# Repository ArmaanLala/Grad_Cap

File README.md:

# Graduation Cap
A PCB Design to wear on my Grad Cap for Spring 2023 commencement.

#### Important links

MicroController
https://www.adafruit.com/product/4481

## Schematic and Board layout

- Add images later

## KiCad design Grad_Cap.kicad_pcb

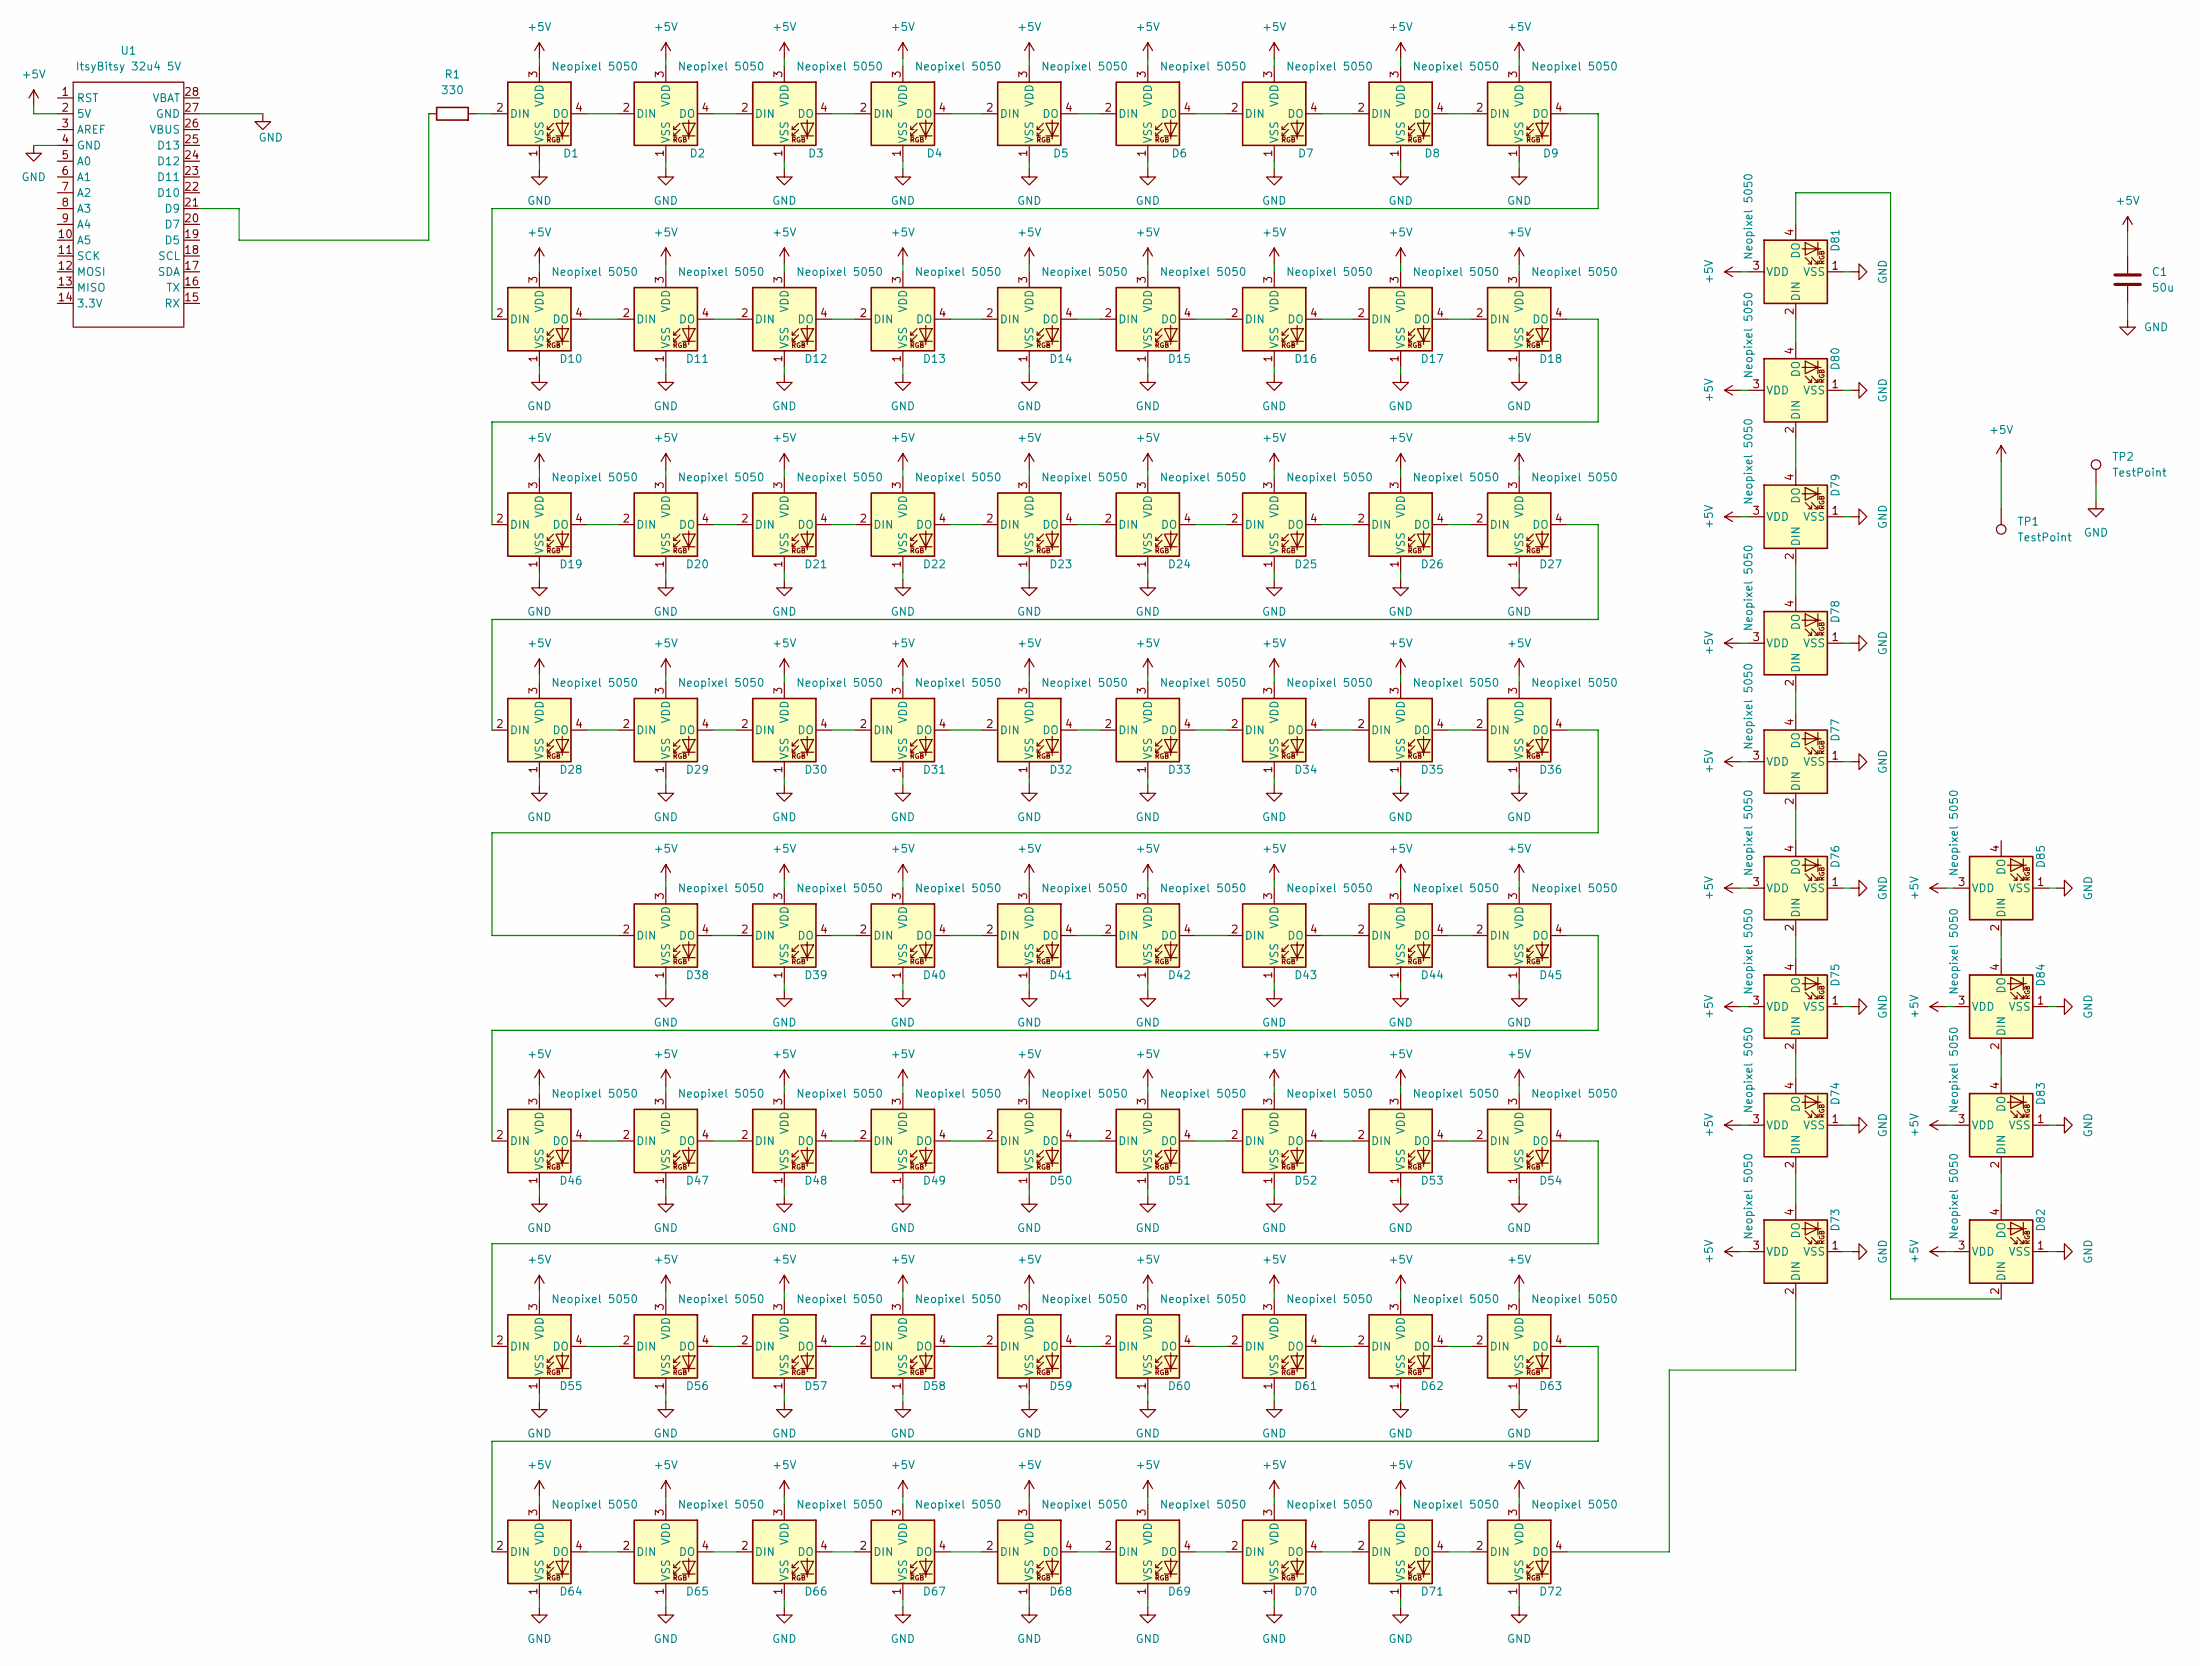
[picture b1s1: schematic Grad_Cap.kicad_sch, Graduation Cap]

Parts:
C1: 50u; C_1206_3216Metric_Pad1.33x1.80mm_HandSolder
D1, D2, D3, D4, D5, D6, D7, D8, D9, D10, D11, D12, D13, D14, D15, D16, D17, D18, D19, D20, D21, D22, D23, D24, D25, D26, D27, D28, D29, D30, D31, D32, D33, D34, D35, D36, D38, D39, D40, D41, D42, D43, D44, D45, D46, D47, D48, D49, D50, D51, D52, D53, D54, D55, D56, D57, D58, D59, D60, D61, D62, D63, D64, D65, D66, D67, D68, D69, D70, D71, D72, D73, D74, D75, D76, D77, D78, D79, D80, D81, D82, D83, D84, D85: Neopixel 5050; LED_Inolux_IN-PI554FCH_PLCC4_5.0x5.0mm_P3.2mm
R1: 330; R_1206_3216Metric_Pad1.30x1.75mm_HandSolder
TP1, TP2: TestPoint; TestPoint_Pad_4.0x4.0mm
U1: ItsyBitsy 32u4 5V; DIP-28_W15.24mm_LongPads

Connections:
+5V: C1.1, D1.3 (VDD), D2.3 (VDD), D3.3 (VDD), D4.3 (VDD), D5.3 (VDD), D6.3 (VDD), D7.3 (VDD), D8.3 (VDD), D9.3 (VDD), D10.3 (VDD), D11.3 (VDD), D12.3 (VDD), D13.3 (VDD), D14.3 (VDD), D15.3 (VDD), D16.3 (VDD), D17.3 (VDD), D18.3 (VDD), D19.3 (VDD), D20.3 (VDD), D21.3 (VDD), D22.3 (VDD), D23.3 (VDD), D24.3 (VDD), D25.3 (VDD), D26.3 (VDD), D27.3 (VDD), D28.3 (VDD), D29.3 (VDD), D30.3 (VDD), D31.3 (VDD), D32.3 (VDD), D33.3 (VDD), D34.3 (VDD), D35.3 (VDD), D36.3 (VDD), D38.3 (VDD), D39.3 (VDD), D40.3 (VDD), D41.3 (VDD), D42.3 (VDD), D43.3 (VDD), D44.3 (VDD), D45.3 (VDD), D46.3 (VDD), D47.3 (VDD), D48.3 (VDD), D49.3 (VDD), D50.3 (VDD), D51.3 (VDD), D52.3 (VDD), D53.3 (VDD), D54.3 (VDD), D55.3 (VDD), D56.3 (VDD), D57.3 (VDD), D58.3 (VDD), D59.3 (VDD), D60.3 (VDD), D61.3 (VDD), D62.3 (VDD), D63.3 (VDD), D64.3 (VDD), D65.3 (VDD), D66.3 (VDD), D67.3 (VDD), D68.3 (VDD), D69.3 (VDD), D70.3 (VDD), D71.3 (VDD), D72.3 (VDD), D73.3 (VDD), D74.3 (VDD), D75.3 (VDD), D76.3 (VDD), D77.3 (VDD), D78.3 (VDD), D79.3 (VDD), D80.3 (VDD), D81.3 (VDD), D82.3 (VDD), D83.3 (VDD), D84.3 (VDD), D85.3 (VDD), TP1.1, U1.2 (5V)
GND: C1.2, D1.1 (VSS), D2.1 (VSS), D3.1 (VSS), D4.1 (VSS), D5.1 (VSS), D6.1 (VSS), D7.1 (VSS), D8.1 (VSS), D9.1 (VSS), D10.1 (VSS), D11.1 (VSS), D12.1 (VSS), D13.1 (VSS), D14.1 (VSS), D15.1 (VSS), D16.1 (VSS), D17.1 (VSS), D18.1 (VSS), D19.1 (VSS), D20.1 (VSS), D21.1 (VSS), D22.1 (VSS), D23.1 (VSS), D24.1 (VSS), D25.1 (VSS), D26.1 (VSS), D27.1 (VSS), D28.1 (VSS), D29.1 (VSS), D30.1 (VSS), D31.1 (VSS), D32.1 (VSS), D33.1 (VSS), D34.1 (VSS), D35.1 (VSS), D36.1 (VSS), D38.1 (VSS), D39.1 (VSS), D40.1 (VSS), D41.1 (VSS), D42.1 (VSS), D43.1 (VSS), D44.1 (VSS), D45.1 (VSS), D46.1 (VSS), D47.1 (VSS), D48.1 (VSS), D49.1 (VSS), D50.1 (VSS), D51.1 (VSS), D52.1 (VSS), D53.1 (VSS), D54.1 (VSS), D55.1 (VSS), D56.1 (VSS), D57.1 (VSS), D58.1 (VSS), D59.1 (VSS), D60.1 (VSS), D61.1 (VSS), D62.1 (VSS), D63.1 (VSS), D64.1 (VSS), D65.1 (VSS), D66.1 (VSS), D67.1 (VSS), D68.1 (VSS), D69.1 (VSS), D70.1 (VSS), D71.1 (VSS), D72.1 (VSS), D73.1 (VSS), D74.1 (VSS), D75.1 (VSS), D76.1 (VSS), D77.1 (VSS), D78.1 (VSS), D79.1 (VSS), D80.1 (VSS), D81.1 (VSS), D82.1 (VSS), D83.1 (VSS), D84.1 (VSS), D85.1 (VSS), TP2.1, U1.4 (GND), U1.27 (GND)
unnamed: D1.2 (DIN), R1.2
unnamed: D1.4 (DO), D2.2 (DIN)
unnamed: D2.4 (DO), D3.2 (DIN)
unnamed: D3.4 (DO), D4.2 (DIN)
unnamed: D4.4 (DO), D5.2 (DIN)
unnamed: D5.4 (DO), D6.2 (DIN)
unnamed: D6.4 (DO), D7.2 (DIN)
unnamed: D7.4 (DO), D8.2 (DIN)
unnamed: D8.4 (DO), D9.2 (DIN)
unnamed: D9.4 (DO), D10.2 (DIN)
unnamed: D10.4 (DO), D11.2 (DIN)
unnamed: D11.4 (DO), D12.2 (DIN)
unnamed: D12.4 (DO), D13.2 (DIN)
unnamed: D13.4 (DO), D14.2 (DIN)
unnamed: D14.4 (DO), D15.2 (DIN)
unnamed: D15.4 (DO), D16.2 (DIN)
unnamed: D16.4 (DO), D17.2 (DIN)
unnamed: D17.4 (DO), D18.2 (DIN)
unnamed: D18.4 (DO), D19.2 (DIN)
unnamed: D19.4 (DO), D20.2 (DIN)
unnamed: D20.4 (DO), D21.2 (DIN)
unnamed: D21.4 (DO), D22.2 (DIN)
unnamed: D22.4 (DO), D23.2 (DIN)
unnamed: D23.4 (DO), D24.2 (DIN)
unnamed: D24.4 (DO), D25.2 (DIN)
unnamed: D25.4 (DO), D26.2 (DIN)
unnamed: D26.4 (DO), D27.2 (DIN)
unnamed: D27.4 (DO), D28.2 (DIN)
unnamed: D28.4 (DO), D29.2 (DIN)
unnamed: D29.4 (DO), D30.2 (DIN)
unnamed: D30.4 (DO), D31.2 (DIN)
unnamed: D31.4 (DO), D32.2 (DIN)
unnamed: D32.4 (DO), D33.2 (DIN)
unnamed: D33.4 (DO), D34.2 (DIN)
unnamed: D34.4 (DO), D35.2 (DIN)
unnamed: D35.4 (DO), D36.2 (DIN)
unnamed: D36.4 (DO), D38.2 (DIN)
unnamed: D38.4 (DO), D39.2 (DIN)
unnamed: D39.4 (DO), D40.2 (DIN)
unnamed: D40.4 (DO), D41.2 (DIN)
unnamed: D41.4 (DO), D42.2 (DIN)
unnamed: D42.4 (DO), D43.2 (DIN)
unnamed: D43.4 (DO), D44.2 (DIN)
unnamed: D44.4 (DO), D45.2 (DIN)
unnamed: D45.4 (DO), D46.2 (DIN)
unnamed: D46.4 (DO), D47.2 (DIN)
unnamed: D47.4 (DO), D48.2 (DIN)
unnamed: D48.4 (DO), D49.2 (DIN)
unnamed: D49.4 (DO), D50.2 (DIN)
unnamed: D50.4 (DO), D51.2 (DIN)
unnamed: D51.4 (DO), D52.2 (DIN)
unnamed: D52.4 (DO), D53.2 (DIN)
unnamed: D53.4 (DO), D54.2 (DIN)
unnamed: D54.4 (DO), D55.2 (DIN)
unnamed: D55.4 (DO), D56.2 (DIN)
unnamed: D56.4 (DO), D57.2 (DIN)
unnamed: D57.4 (DO), D58.2 (DIN)
unnamed: D58.4 (DO), D59.2 (DIN)
unnamed: D59.4 (DO), D60.2 (DIN)
unnamed: D60.4 (DO), D61.2 (DIN)
unnamed: D61.4 (DO), D62.2 (DIN)
unnamed: D62.4 (DO), D63.2 (DIN)
unnamed: D63.4 (DO), D64.2 (DIN)
unnamed: D64.4 (DO), D65.2 (DIN)
unnamed: D65.4 (DO), D66.2 (DIN)
unnamed: D66.4 (DO), D67.2 (DIN)
unnamed: D67.4 (DO), D68.2 (DIN)
unnamed: D68.4 (DO), D69.2 (DIN)
unnamed: D69.4 (DO), D70.2 (DIN)
unnamed: D70.4 (DO), D71.2 (DIN)
unnamed: D71.4 (DO), D72.2 (DIN)
unnamed: D72.4 (DO), D73.2 (DIN)
unnamed: D73.4 (DO), D74.2 (DIN)
unnamed: D74.4 (DO), D75.2 (DIN)
unnamed: D75.4 (DO), D76.2 (DIN)
unnamed: D76.4 (DO), D77.2 (DIN)
unnamed: D77.4 (DO), D78.2 (DIN)
unnamed: D78.4 (DO), D79.2 (DIN)
unnamed: D79.4 (DO), D80.2 (DIN)
unnamed: D80.4 (DO), D81.2 (DIN)
unnamed: D81.4 (DO), D82.2 (DIN)
unnamed: D82.4 (DO), D83.2 (DIN)
unnamed: D83.4 (DO), D84.2 (DIN)
unnamed: D84.4 (DO), D85.2 (DIN)
unnamed: R1.1, U1.21 (D9)

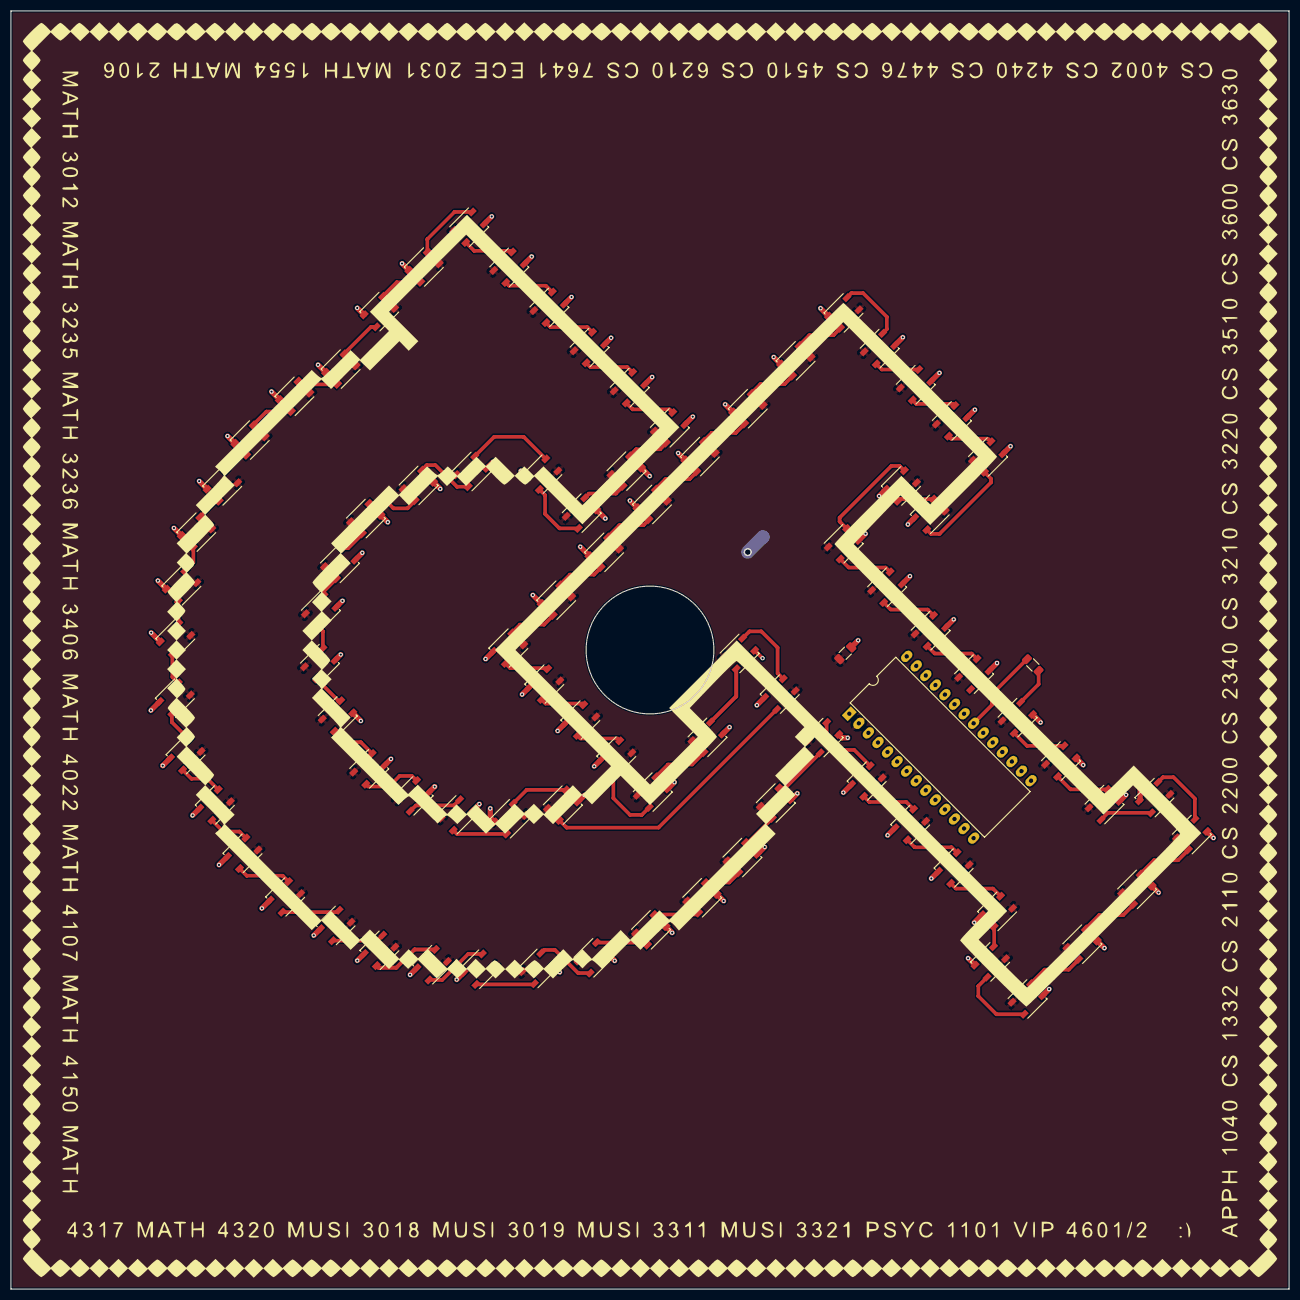
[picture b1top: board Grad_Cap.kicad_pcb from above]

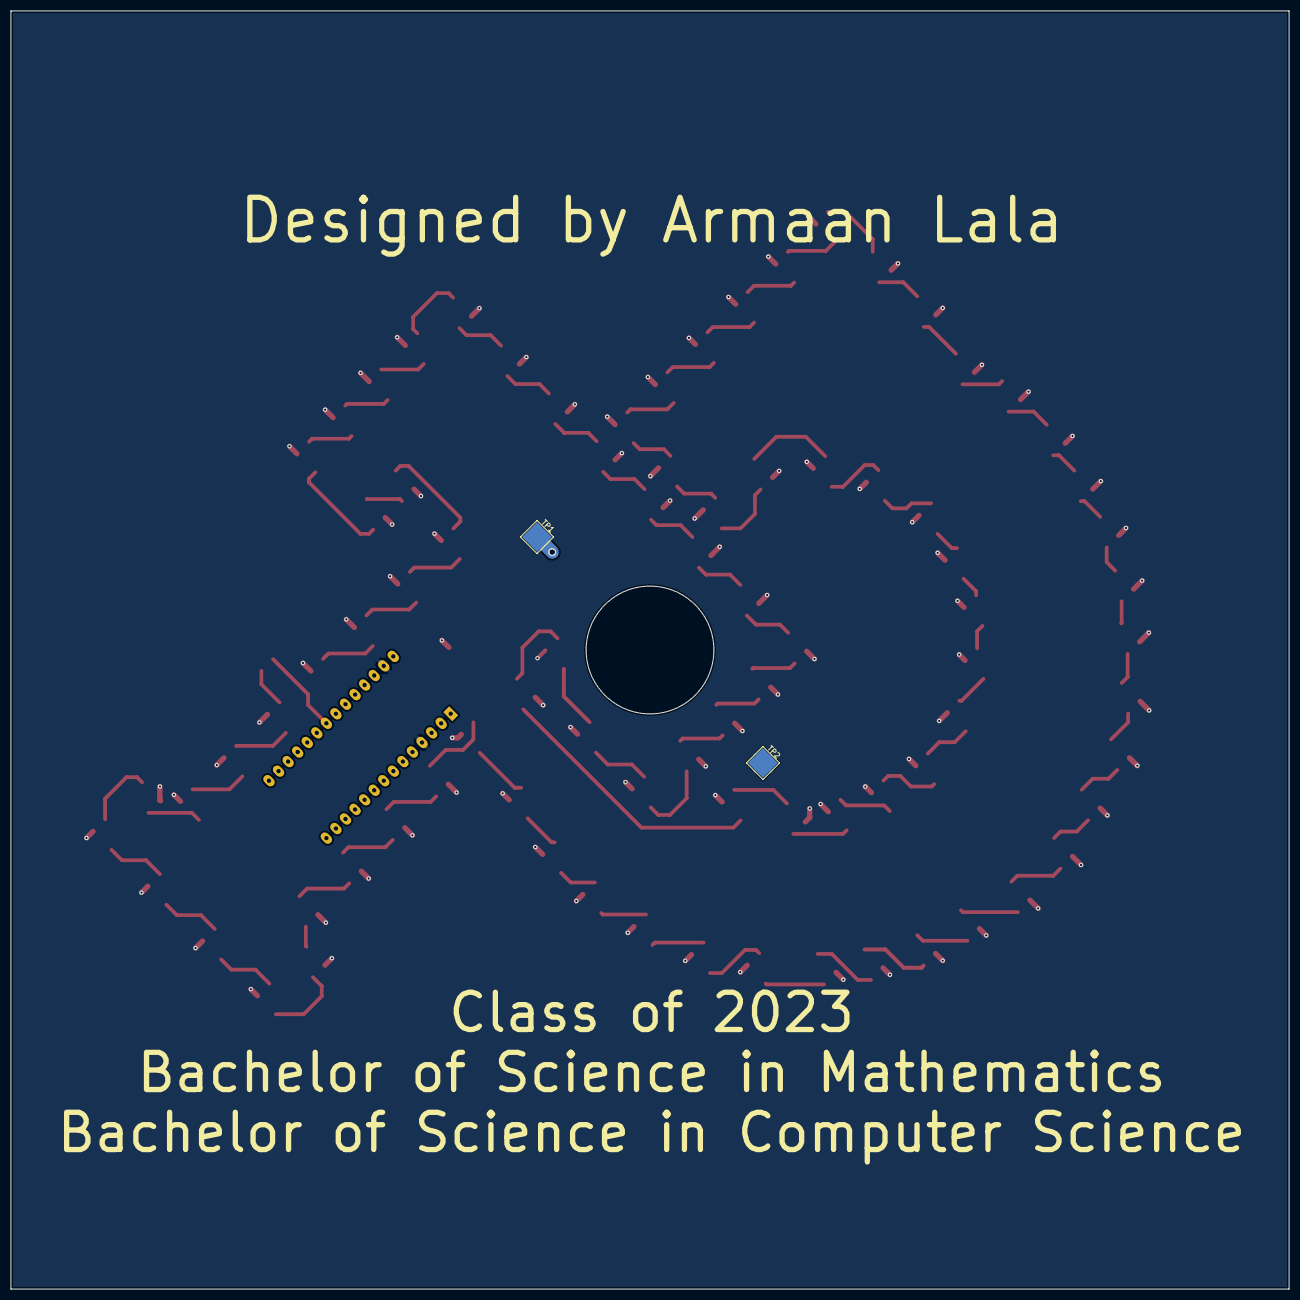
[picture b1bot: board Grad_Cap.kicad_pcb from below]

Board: 2 copper layers, 240.0 x 240.0 mm, 89 parts (2 on the bottom side), 87 nets.

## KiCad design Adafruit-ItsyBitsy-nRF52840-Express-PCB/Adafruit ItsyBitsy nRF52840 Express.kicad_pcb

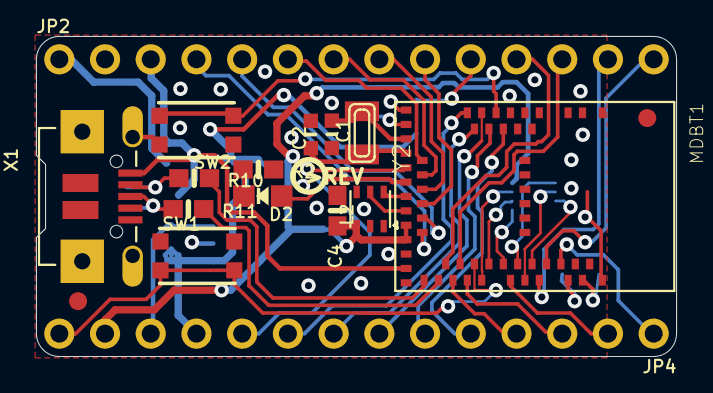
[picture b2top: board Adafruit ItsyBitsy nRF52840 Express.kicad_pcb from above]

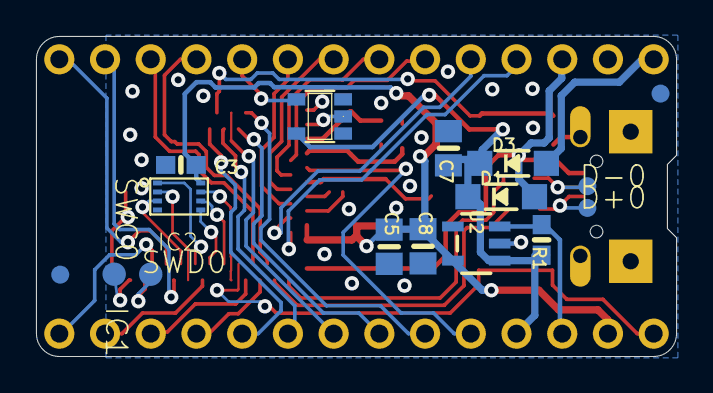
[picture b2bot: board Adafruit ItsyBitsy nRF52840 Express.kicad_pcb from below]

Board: 2 copper layers, 35.6 x 17.8 mm, 36 parts (17 on the bottom side), 48 nets.

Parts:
C1, C2: 22pF; _0603MP
C3, C4: 0.1uF; 0603-NO
C5, C7, C8: 10uF; 0805-NO
D1, D3: MBR120; SOD-123
D2: RED; CHIPLED_0805_NOOUTLINE
D+0: TPTP10R; TP10R
D-0: TPTP10R; TP10R
FID1, FID2, FID3, FID4: FIDUCIAL_1MM
IC1: 74HCT1G125DBV; SOT23-5
IC2: GD25Q16; USON8
JP2, JP4: 1X14_ROUND70
L2: AP102-2020; APA102_2020
MDBT1: MDBT50
R1: 10K; 0603-NO
R2: 1K; 0603-NO
R10, R11: 22; 0603-NO
SW1, SW2: KMR2; BTN_KMR2_4.6X2.8
SWC0: TPTP13R; TP13R
SWD0: TPTP13R; TP13R
U2: AP2112(3.3V); SOT23-5
U$12: ITSYNRF52840_TOP
U$14: ITSYNRF52840_BOT
U$15: PCBFEAT-REV-040
X1: 4u20329; 4UCONN_20329_V2
Y2: 32.768; XTAL3215

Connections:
3.3V: C3.2, C4.2, C5.2, C8.2, IC2.8, JP4.13, L2.3, MDBT1.28, MDBT1.30, U2.5
A0: JP4.10, MDBT1.20
A1: JP4.9, MDBT1.14
A2: JP4.8, MDBT1.13
A3: JP4.7, MDBT1.12
A4: JP4.6, MDBT1.11
A5: JP4.5, MDBT1.9
D2: JP4.1, MDBT1.50
D5: IC1.2, MDBT1.16
D5_5V: IC1.4, JP2.10
D7: JP2.9, MDBT1.25
D9: JP2.8, MDBT1.23
D10: JP2.7, MDBT1.21
D11: JP2.6, MDBT1.19
D12: JP2.5, MDBT1.27
D13: JP2.4, MDBT1.29
D+: D+0.TP, R11.1, X1.D+
D-: D-0.TP, R10.1, X1.D-
DOT_CLK: L2.5, MDBT1.26
DOT_DATA: L2.6, MDBT1.24
EN: JP4.12, R1.1, U2.3
GND: C1.2, C2.2, C3.1, C4.1, C5.1, C7.1, C8.1, IC1.1, IC1.3, IC2.4, JP2.2, L2.4, MDBT1.1, MDBT1.2, MDBT1.15, MDBT1.33, MDBT1.55, R2.2, SW1.A, SW1.A', SW2.A, SW2.A', U2.2, X1.BASE@1, X1.BASE@2, X1.GND, X1.SPRT@1, X1.SPRT@2, X1.SPRT@3, X1.SPRT@4
LED1: D2.A, MDBT1.22
MISO: JP4.2, MDBT1.44
MOSI: JP4.3, MDBT1.39
unnamed: D2.C, R2.1
unnamed: C1.1, MDBT1.17, Y2.P$1
unnamed: C2.1, MDBT1.18, Y2.P$2
QSPI_CS: IC2.1, MDBT1.45
QSPI_DATA0: IC2.5, MDBT1.43
QSPI_DATA1: IC2.2, MDBT1.46
QSPI_DATA2: IC2.3, MDBT1.47
QSPI_DATA3: IC2.7, MDBT1.41
QSPI_SCK: IC2.6, MDBT1.42
RX_D0: JP2.14, MDBT1.49
SCK: JP4.4, MDBT1.37
SCL: JP2.11, MDBT1.36
SDA: JP2.12, MDBT1.38
SWCLK: MDBT1.53, SWC0.TP
SWDIO: MDBT1.51, SWD0.TP
SWITCH: MDBT1.10, SW2.B, SW2.B'
TX_D1: JP2.13, MDBT1.48
USBD+: MDBT1.35, R11.2
USBD-: MDBT1.34, R10.2
VBAT: D3.A, JP2.1
VBUS: D1.A, JP2.3, MDBT1.32, X1.VBUS
VHI: C7.2, D1.C, D3.C, IC1.5, JP4.11, R1.2, U2.1
~RESET: JP4.14, MDBT1.40, SW1.B, SW1.B'

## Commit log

2022-12-23 update part
2022-12-23 Cleaning files
2022-12-23 Readme
2023-01-03 Test Commit
2023-01-25 Added neopixels
2023-01-30 Test shtuff
2023-01-30 Initial Layout done
2023-01-31 It looks pretty
2023-01-31 routing time
2023-02-01 ground vias?
2023-02-08 Routing and pours done
2023-02-15 cap + refs gone
2023-02-17 Pads Added
2023-02-17 Dip Switch
2023-02-20 Design has been ordered
2023-02-20 Hopefully done
2023-04-09 Last checkpoint
2023-04-10 New Design
2023-04-10 Reordering Designs
2023-12-20 Adding final design
